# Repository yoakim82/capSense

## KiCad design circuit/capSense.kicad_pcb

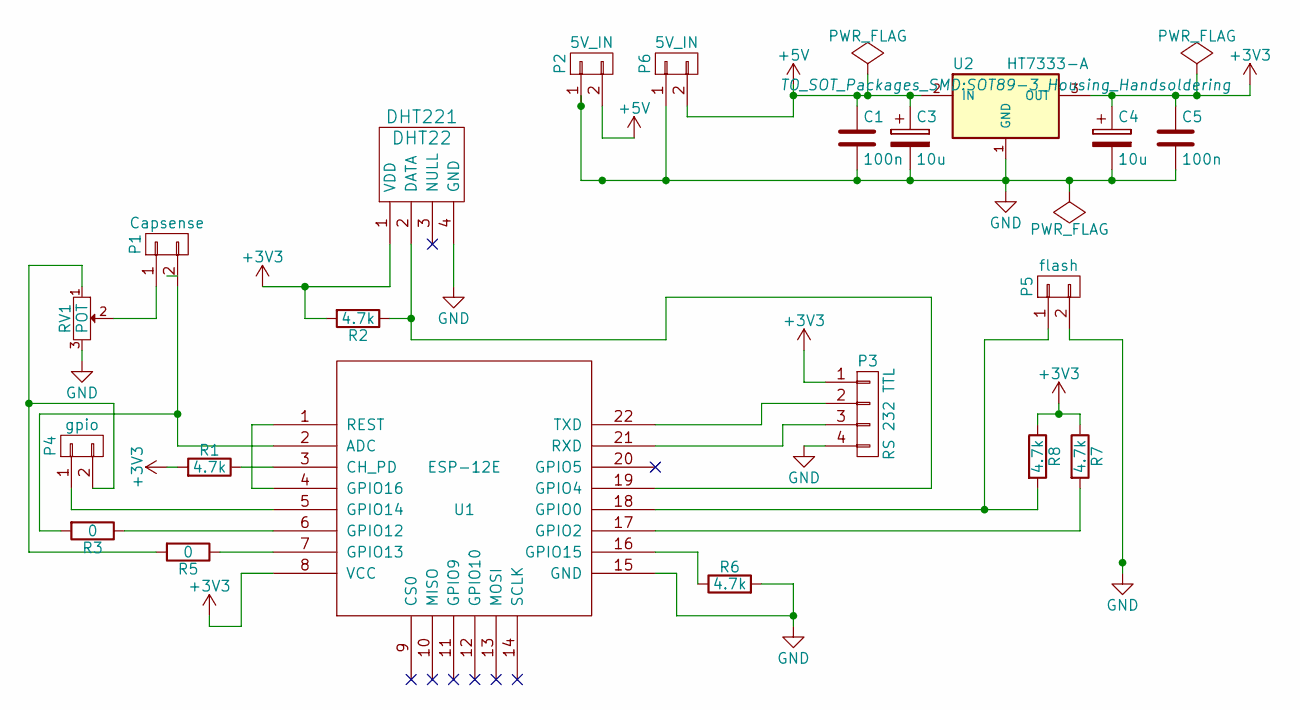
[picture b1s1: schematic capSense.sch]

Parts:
C1, C5: 100n; C_0805_HandSoldering
C3, C4: 10u; TantalC_SizeC_EIA-6032_HandSoldering
DHT221: DHT22; Pin_Header_Straight_1x04
P1: Capsense; Socket_Strip_Straight_1x02
P2, P6: 5V_IN; Socket_Strip_Straight_1x02
P3: RS 232 TTL; Socket_Strip_Straight_1x04
P4: gpio; Socket_Strip_Straight_1x02
P5: flash; Socket_Strip_Straight_1x02
R1, R2, R6, R7, R8: 4.7k; R_0805_HandSoldering
R3, R5: 0; R_0805_HandSoldering
RV1: POT; Potentiometer_Bourns_3296Z_3-8Zoll_Angular_ScrewFront
U1: ESP-12E
U2: HT7333-A; SOT89-3_Housing_Handsoldering

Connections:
+3V3: C4.1, C5.1, DHT221.1 (VDD), P3.1, R1.2, R2.2, R7.1, R8.1, U1.8 (VCC), U2.3 (OUT)
+5V: C1.1, C3.1, P2.2, P6.2, U2.2 (IN)
GND: C1.2, C3.2, C4.2, C5.2, DHT221.4 (GND), P2.1, P3.4, P5.2, P6.1, R6.2, RV1.3, U1.15 (GND), U2.1 (GND)
unnamed: DHT221.2 (DATA), R2.1, U1.19 (GPIO4)
unnamed: P1.1, RV1.2
unnamed: P1.2, R3.2, U1.2 (ADC)
unnamed: P3.2, U1.22 (TXD)
unnamed: P3.3, U1.21 (RXD)
unnamed: P4.1, U1.5 (GPIO14)
unnamed: P4.2, R5.2, RV1.1
unnamed: P5.1, R8.2, U1.18 (GPIO0)
unnamed: R1.1, U1.3 (CH_PD)
unnamed: R3.1, U1.6 (GPIO12)
unnamed: R5.1, U1.7 (GPIO13)
unnamed: R6.1, U1.16 (GPIO15)
unnamed: R7.2, U1.17 (GPIO2)
unnamed: U1.1 (REST), U1.4 (GPIO16)

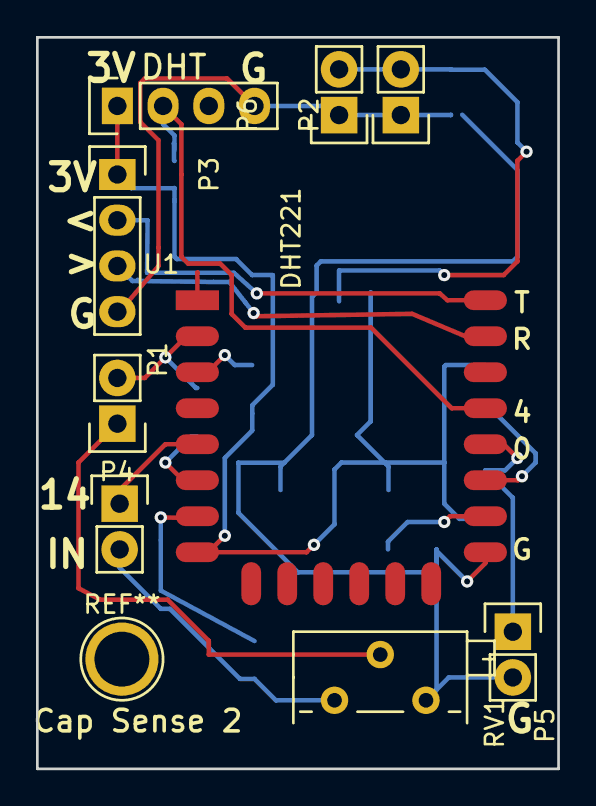
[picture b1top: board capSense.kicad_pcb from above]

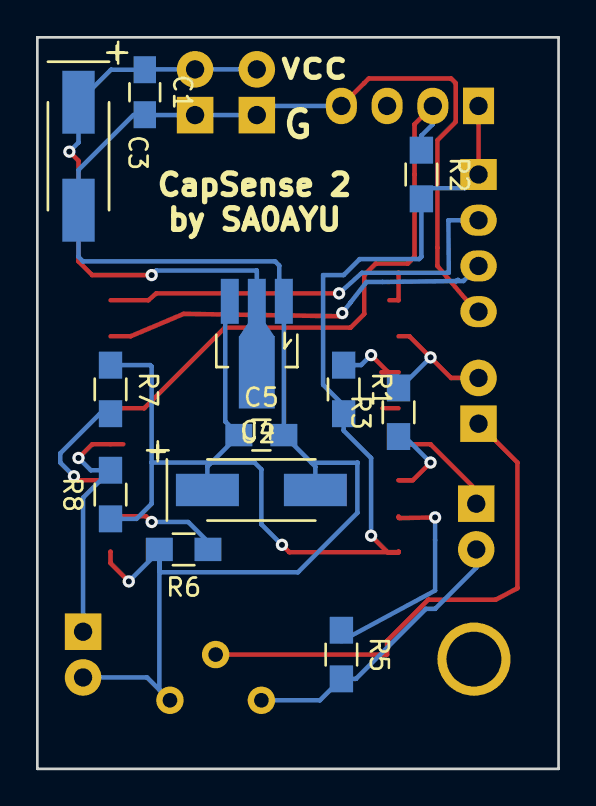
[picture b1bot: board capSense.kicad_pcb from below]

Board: 2 copper layers, 29.0 x 40.6 mm, 21 parts (12 on the bottom side), 17 nets.

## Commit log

2016-07-01 added init file w removed wifi credentials
2016-08-03 new version of PCB with support for waterlog
